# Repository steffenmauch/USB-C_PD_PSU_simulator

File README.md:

# USB-C_PD_PSU_simulator

USB-C PD power supply simulator based on STUSB4710 with CP2112 USB/I2C interface chip

### Introduction

- USB-C power delivery powers supply simulator based on STUSB4710
- can be used to simulated non conformant power supplies
- e.g. output different voltage than the one being negotiated
- manipulate offered contracts to simulate specific power supplies
- layout and schematic has been realized with KiCad 6
- correspondig software is written with python 3
- communication with STUSB4710 is realized with SiLabs 2112 USB to I2C/SMBUS interface chip

### Hardware Setup

Find schematic as PDF [here](./ECAD/USB-C_PSU_Simulator.pdf)

### Usage
- install python3 if not already installed; e.g. https://winpython.github.io/ for Windows users
- download from www.silabs.com the driver containing the files 'SLABHIDDevice.*' and 'SLABHIDtoSMBus.*' (extension .dll for Windows)
- copy both files into 'Software' subdirectory
- execute e.g. 'python configSTUSB4710.py' in the 'Software' subdirectory
```
python configSTUSB4710.py
usage: configSTUSB4710.py [-h] [-r] [--setToleranceVBUS [0-15]] [--setPDO SETPDO [SETPDO ...]] [--printRDO] [--printPDO] [--printNVM] [--printToleranceVBUS] [--printVBUSControl] [--printPortStatus]
                          [--printSTUSBVersion] [-v]

Configure STUSB4710 for USB-C PD power supply simulation; (c) 12/2022 Steffen Mauch; MIT license

optional arguments:
  -h, --help            show this help message and exit
  -r, --resetSTUSB      reset STUSB4710 via command
  --setToleranceVBUS [0-15]
                        set additional VBUS tolerance in percent of STUSB4710
  --setPDO SETPDO [SETPDO ...]
                        modify PDO of STUSB4710; first argument selects #PDO;second argument voltage in [mv]; third argument current in [mA] e.g. 1 5000 2000 will set PDO1 to 5V and 2A
  --printRDO            shows actual settings requested data object (RDO) of STUSB4710
  --printPDO            shows actual settings power data object (PDO) of STUSB4710
  --printNVM            shows actual content of non volatile memory (NVM) of STUSB4710
  --printToleranceVBUS  get full VBUS tolerance in percent of STUSB4710 [incl. 5 percent default]
  --printVBUSControl    get VBUS control register of STUSB4710
  --printPortStatus     get port status register of STUSB4710
  --printSTUSBVersion   get version register of STUSB4710
  -v, --version         show version of python script
```
- show advertised src of USB-C PD
```
python configSTUSB4710.py --printPDO

PDO SRC#1:  PdoSink(voltage=5.0V, current=3.0A, fastRoleReqCur=0, dualRoleData=0, usbCommunicationsCapable=0, unconstrainedPower=1, higherCapability=0, dualRolePower=0, supply=Fixed, raw=0x0801912c)
PDO SRC#2:  PdoSink(voltage=9.0V, current=3.0A, fastRoleReqCur=0, dualRoleData=0, usbCommunicationsCapable=0, unconstrainedPower=0, higherCapability=0, dualRolePower=0, supply=Fixed, raw=0x0002d12c)
PDO SRC#3:  PdoSink(voltage=12.0V, current=3.0A, fastRoleReqCur=0, dualRoleData=0, usbCommunicationsCapable=0, unconstrainedPower=0, higherCapability=0, dualRolePower=0, supply=Fixed, raw=0x0003c12c)
PDO SRC#4:  PdoSink(voltage=15.0V, current=3.0A, fastRoleReqCur=0, dualRoleData=0, usbCommunicationsCapable=0, unconstrainedPower=0, higherCapability=0, dualRolePower=0, supply=Fixed, raw=0x0004b12c)
PDO SRC#5:  PdoSink(voltage=20.0V, current=2.25A, fastRoleReqCur=0, dualRoleData=0, usbCommunicationsCapable=0, unconstrainedPower=0, higherCapability=0, dualRolePower=0, supply=Fixed, raw=0x000640e1)
```

### Background information for STUSB4710
- 'dm00664189-the-stusb4500-software-programing-guide-stmicroelectronics.pdf'
- 'STUSB47xx_register_map_public.pdf'
- 'STSW-STUSB004 - Quick Start - v1.0.pdf'
- 'TNxxx - STUSB4500 NVM Description_V1.1.pdf' and 'TNxxx - STUSB4700 NVM Description.pdf' which is part of 'STSW-STUSB003' and STSW-STUSB004'

### Background information for CP2112
- API information can be found in 'AN496.pdf'

### License

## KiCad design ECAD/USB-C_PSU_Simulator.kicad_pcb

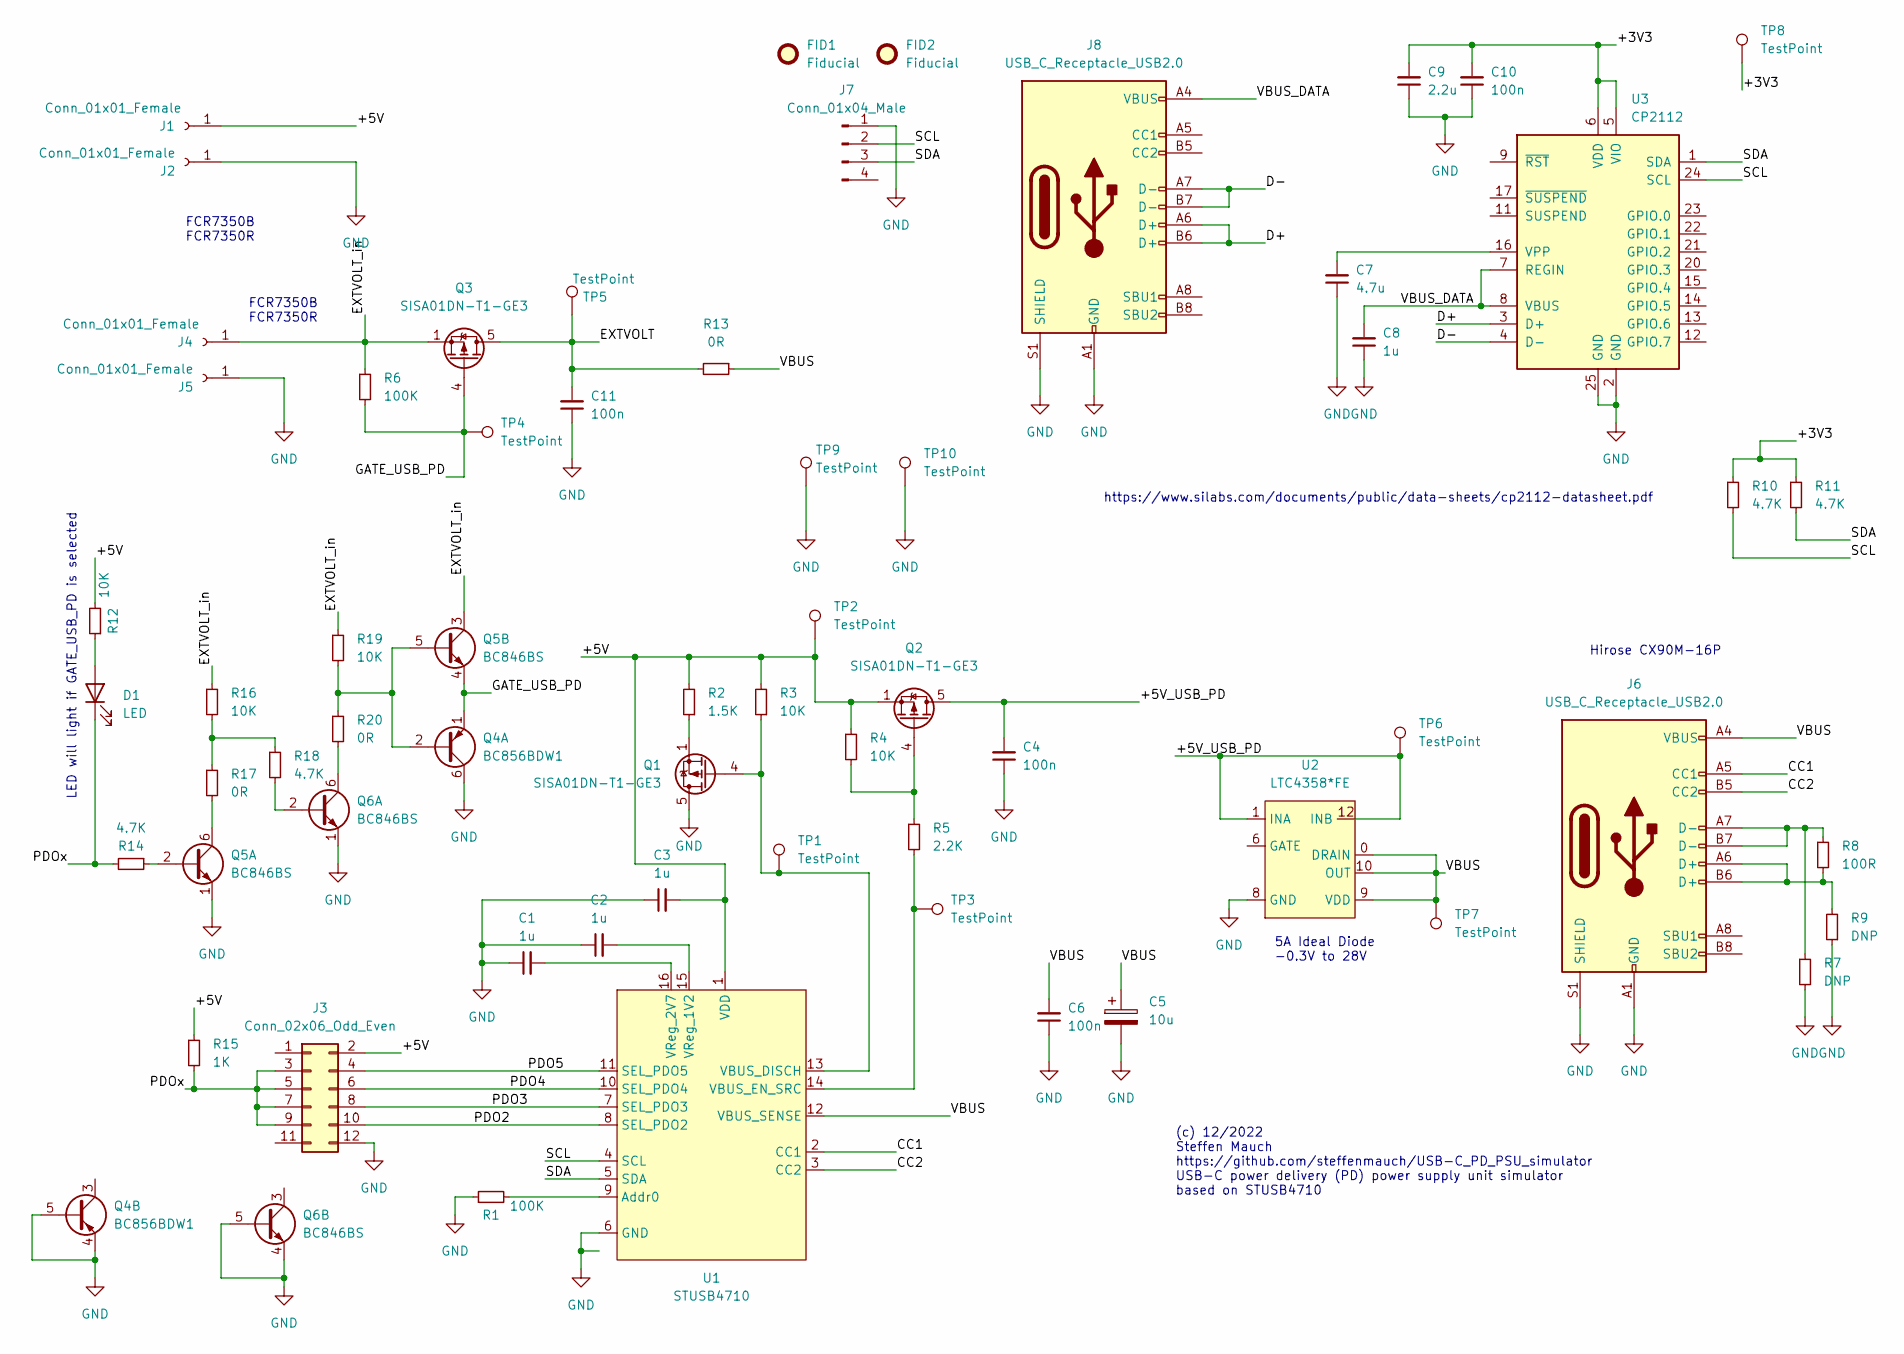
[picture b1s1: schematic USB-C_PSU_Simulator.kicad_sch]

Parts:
C1, C2, C3, C8: 1u; C_0603_1608Metric
C4, C10, C11: 100n; C_0603_1608Metric
C5: 10u; CP_Elec_6.3x5.4_Nichicon
C6: 100n; C_1206_3216Metric
C7: 4.7u; C_0603_1608Metric
C9: 2.2u; C_0603_1608Metric
D1: LED; LED_0603_1608Metric
FID1, FID2: Fiducial; Fiducial_1mm_Mask2mm
J1, J2, J4, J5: Conn_01x01_Female; FCR7350
J3: Conn_02x06_Odd_Even; PinHeader_2x06_P2.54mm_Vertical
J6, J8: USB_C_Receptacle_USB2.0; USB_C_Receptacle_Hirose_CX90M-16P
J7: Conn_01x04_Male; JST_PH_B4B-PH-K_1x04_P2.00mm_Vertical
Q1, Q2, Q3: SISA01DN-T1-GE3; Vishay_PowerPAK_1212-8_Single
Q4: BC856BDW1; SOT-363_SC-70-6
Q5, Q6: BC846BS; SOT-363_SC-70-6
R1, R6: 100K; R_0603_1608Metric
R2: 1.5K; R_0603_1608Metric
R3, R4, R12, R16, R19: 10K; R_0603_1608Metric
R5: 2.2K; R_0603_1608Metric
R7, R9: DNP; R_0603_1608Metric
R8: 100R; R_0603_1608Metric
R10, R11, R14, R18: 4.7K; R_0603_1608Metric
R13, R17, R20: 0R; R_0603_1608Metric
R15: 1K; R_0603_1608Metric
TP1, TP2, TP3, TP4, TP5, TP6, TP7, TP8, TP9, TP10: TestPoint; TestPoint_THTPad_D1.0mm_Drill0.5mm
U1: STUSB4710; QFN-16_3x3_Pitch0.5mm
U2: LTC4358*FE; 16-LeadPlasticTSSOP_ANALOG
U3: CP2112; QFN-24-1EP_4x4mm_P0.5mm_EP2.6x2.6mm

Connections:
/+3V3: C9.2, C10.2, R10.1, R11.1, TP8.1, U3.5 (VIO), U3.6 (VDD)
/+5V: C3.2, J1.1, J3.2, Q2.1 (S), Q2.2 (S), Q2.3 (S), R2.2, R3.2, R4.1, R12.2, R15.1, TP2.1, U1.1 (VDD)
/CC1: J6.A5 (CC1), U1.2 (CC1)
/CC2: J6.B5 (CC2), U1.3 (CC2)
/D+: J8.A6 (D+), J8.B6 (D+), U3.3 (D+)
/D-: J8.A7 (D-), J8.B7 (D-), U3.4 (D-)
/EXTVOLT: C11.2, Q3.5 (D), R13.2, TP5.1
/EXTVOLT_in: J4.1, Q3.1 (S), Q3.2 (S), Q3.3 (S), Q5.3 (C2), R6.1, R16.1, R19.1
/GATE_USB_PD: Q3.4 (G), Q4.1 (E1), Q5.4 (E2), R6.2, TP4.1
/PDO2: J3.10, U1.8 (SEL_PDO2)
/PDO3: J3.8, U1.7 (SEL_PDO3)
/PDO4: J3.6, U1.10 (SEL_PDO4)
/PDO5: J3.4, U1.11 (SEL_PDO5)
/PDOx: D1.1 (K), J3.3, J3.5, J3.7, J3.9, R14.2, R15.2
/SCL: J7.2, R10.2, U1.4 (SCL), U3.24 (SCL)
/SDA: J7.3, R11.2, U1.5 (SDA), U3.1 (SDA)
/VBUS: C5.1, C6.2, J6.A4 (VBUS), J6.A9 (VBUS), J6.B4 (VBUS), J6.B9 (VBUS), R13.1, TP7.1, U1.12 (VBUS_SENSE), U2.0 (DRAIN), U2.9 (VDD), U2.10 (OUT)
/VBUS_DATA: C8.2, J8.A4 (VBUS), J8.A9 (VBUS), J8.B4 (VBUS), J8.B9 (VBUS), U3.7 (REGIN), U3.8 (VBUS)
GND: C1.1, C2.1, C3.1, C4.1, C5.2, C6.1, C7.1, C8.1, C9.1, C10.1, C11.1, J2.1, J3.12, J5.1, J6.A1 (GND), J6.A12 (GND), J6.B1 (GND), J6.B12 (GND), J6.S1 (SHIELD), J7.1, J8.A1 (GND), J8.A12 (GND), J8.B1 (GND), J8.B12 (GND), J8.S1 (SHIELD), Q1.5 (D), Q4.4 (E2), Q4.5 (B2), Q4.6 (C1), Q5.1 (E1), Q6.1 (E1), Q6.4 (E2), Q6.5 (B2), R1.1, R7.2, R9.1, TP9.1, TP10.1, U1.6 (GND), U2.8 (GND), U3.2 (GND), U3.25 (GND)
IN: C4.2, Q2.5 (D), TP6.1, U2.1 (INA), U2.2 (IN), U2.3 (IN), U2.4 (IN), U2.12 (INB), U2.13 (INB), U2.14 (INB), U2.15 (INB), U2.16 (INB)
unnamed: C1.2, U1.16 (VReg_2V7)
unnamed: C2.2, U1.15 (VReg_1V2)
unnamed: C7.2, U3.16 (VPP)
unnamed: D1.2 (A), R12.1
unnamed: J6.A6 (D+), J6.B6 (D+), R8.2, R9.2
unnamed: J6.A7 (D-), J6.B7 (D-), R7.1, R8.1
unnamed: Q1.1 (S), Q1.2 (S), Q1.3 (S), R2.1
unnamed: Q1.4 (G), R3.1, TP1.1, U1.13 (VBUS_DISCH)
unnamed: Q2.4 (G), R4.2, R5.1
unnamed: Q5.2 (B1), R14.1
unnamed: Q4.2 (B1), Q5.5 (B2), R19.2, R20.1
unnamed: Q5.6 (C1), R17.2
unnamed: Q6.2 (B1), R18.2
unnamed: Q6.6 (C1), R20.2
unnamed: R1.2, U1.9 (Addr0)
unnamed: R5.2, TP3.1, U1.14 (VBUS_EN_SRC)
unnamed: R16.2, R17.1, R18.1

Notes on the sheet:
5A Ideal Diode -0.3V to 28V
Hirose CX90M-16P
https://www.silabs.com/documents/public/data-sheets/cp2112-datasheet.pdf
FCR7350B FCR7350R
LED will light if GATE_USB_PD is selected
(c) 12/2022 Steffen Mauch https://github.com/steffenmauch/USB-C_PD_PSU_simulator USB-C power delivery (PD) power supply unit simulator based on STUSB4710

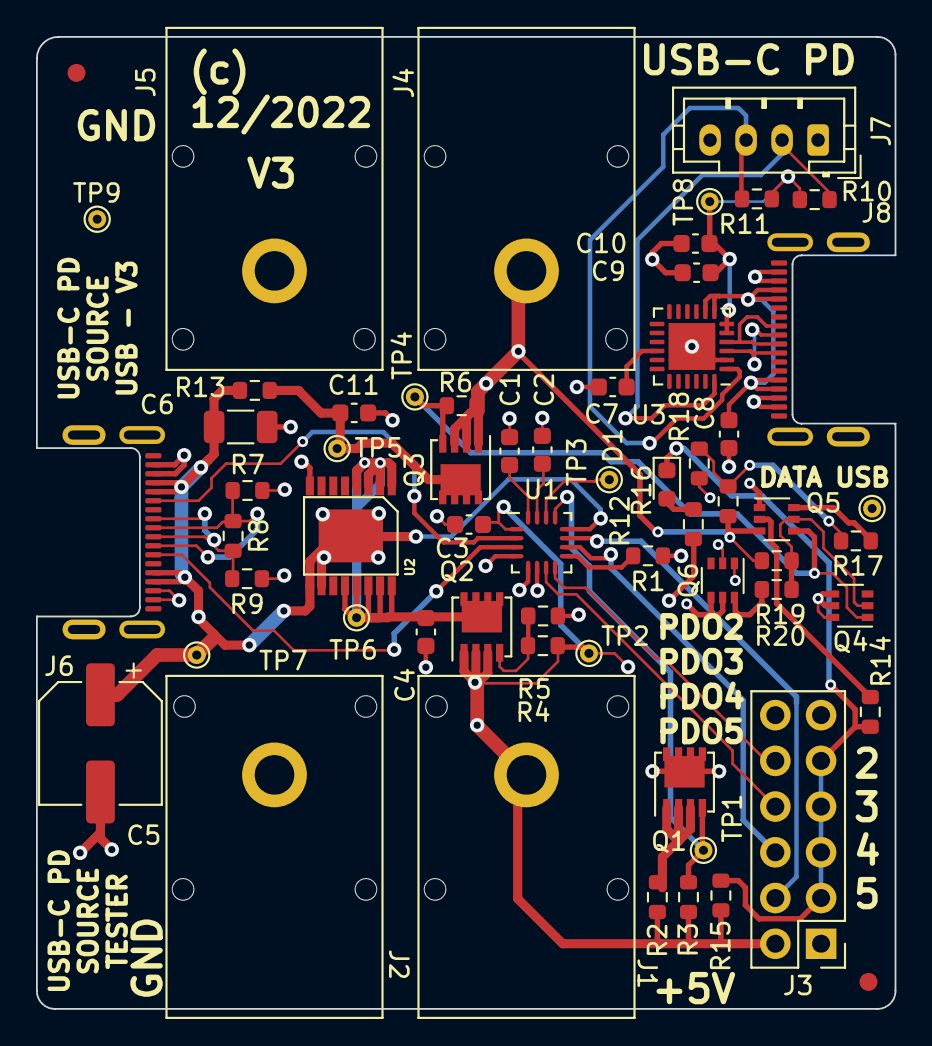
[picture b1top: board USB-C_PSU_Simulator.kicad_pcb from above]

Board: 4 copper layers, 47.7 x 54.0 mm, 61 parts (0 on the bottom side), 37 nets.

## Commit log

2022-12-30 initial commit with schematic and board + LTSpice simulation of transistor stage
2022-12-30 README.md updated
2022-12-31 adding python script to communicate with STUSB4710 USB-C PD source controller improved README.md with additional information added
2022-12-31 fixed naming and indexing of PDOs to match datasheet and naming on PCB

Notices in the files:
README.md:
License:
[License: MIT](https://opensource.org/licenses/MIT)
